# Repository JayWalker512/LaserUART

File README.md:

LaserUART
---------

This is an ongoing project by Peter Mowen and Brandon Foltz to use Arduino compatible microprocessors and other simple hardware to transmit digital information from one computer to another via a laser beam.

Status
------

Currently we are in the planning + resource gathering phase. We have determined that this is possible in principle by conducting simple experiments (and observing that it is done in practice by others already). 

Design
------

The simplest way to accomplish this in principle is by using the built in UART hardware on some Arduino boards. This hardware allows for point-to-point serial communication by connecting TX pins to RX pins on pairs of boards and sending messages across using the Arduino Serial library.

Our approach will leverage this built in hardware to reduce the complexity of external circuitry. The task at hand is to convert these electrical signals from the UART TX pins to photons (via the laser), then convert the received photons back to equivalent electrical signals on the RX (receiving) side.  

Resources
---------

[Lab showing that a photodetector can be constructed using an LED and transistors](https://wiki.analog.com/university/courses/electronics/electronics-lab-led-sensor)

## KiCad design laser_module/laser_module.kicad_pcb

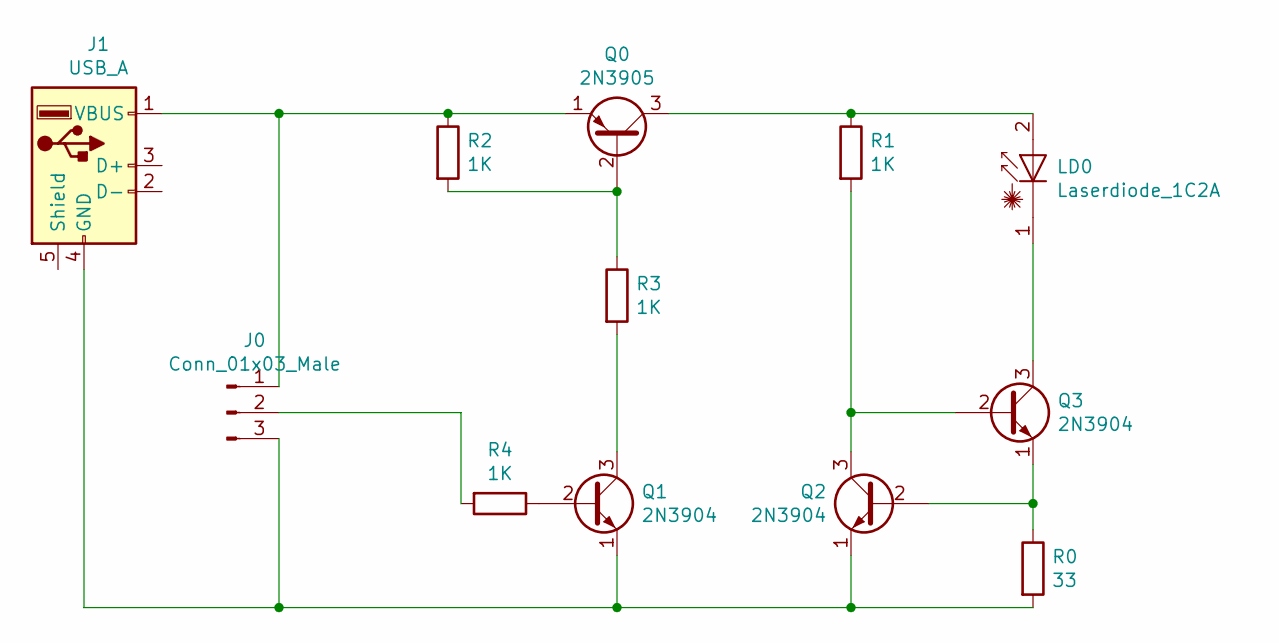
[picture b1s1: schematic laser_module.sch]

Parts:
J0: Conn_01x03_Male; PinHeader_1x03_P2.54mm_Vertical
J1: USB_A; USB_A_CNCTech_1001-011-01101_Horizontal
LD0: Laserdiode_1C2A; LED_D3.0mm
Q0: 2N3905; TO-92_Inline
Q1, Q2, Q3: 2N3904; TO-92_Inline
R0: 33; R_Axial_DIN0207_L6.3mm_D2.5mm_P7.62mm_Horizontal
R1, R2, R3, R4: 1K; R_Axial_DIN0207_L6.3mm_D2.5mm_P7.62mm_Horizontal

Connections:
unnamed: J0.1, J1.1 (VBUS), Q0.1 (E), R2.1
unnamed: J0.2, R4.2
unnamed: J0.3, J1.4 (GND), Q1.1 (E), Q2.1 (E), R0.2
unnamed: LD0.1 (K), Q3.3 (C)
unnamed: LD0.2 (A), Q0.3 (C), R1.1
unnamed: Q0.2 (B), R2.2, R3.1
unnamed: Q1.2 (B), R4.1
unnamed: Q1.3 (C), R3.2
unnamed: Q2.2 (B), Q3.1 (E), R0.1
unnamed: Q2.3 (C), Q3.2 (B), R1.2

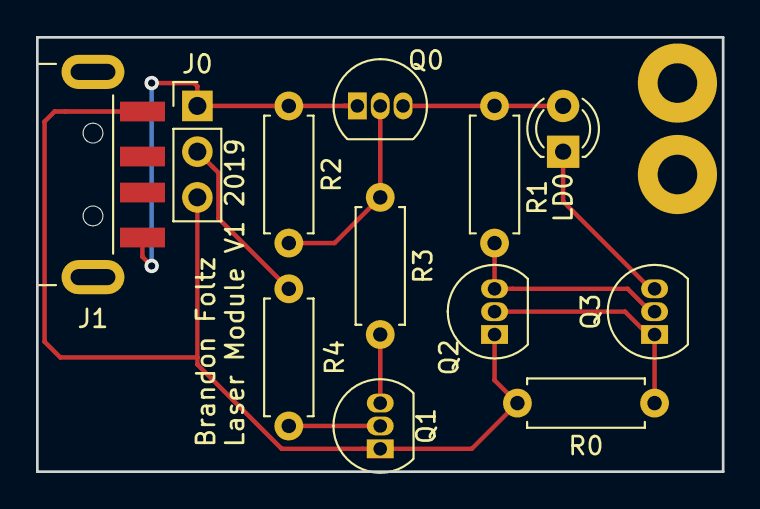
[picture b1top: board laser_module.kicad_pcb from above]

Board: 2 copper layers, 38.1 x 24.1 mm, 12 parts (0 on the bottom side), 10 nets.

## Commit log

2019-03-25 Add KiCad files for the laser diode driver module.
